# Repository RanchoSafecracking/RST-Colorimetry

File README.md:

# RST-Colorimetry
Hardware and firmware for 2015 cheapo colorimeter.

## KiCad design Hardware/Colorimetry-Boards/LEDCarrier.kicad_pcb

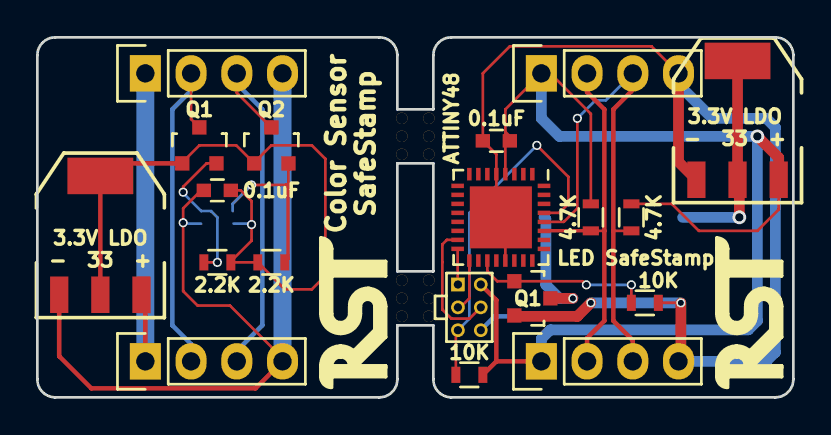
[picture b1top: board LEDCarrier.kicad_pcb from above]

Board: 2 copper layers, 42.0 x 20.0 mm, 21 parts (1 on the bottom side), 18 nets.

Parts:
C1, C2: 0.1uF; C_0603
D1: XREWHT-L1-0000-006E5; XR-E-2-SMD
IC1: ATTINY48-M; QFN-32-1EP_5x5mm_Pitch0.5mm
P1, P2, P4, P5: CONN_01X04; Pin_Header_Straight_1x04
P6: CONN_02X03; PIN-2x3-50MIL
Q1, Q2: 2N7002P; SOT-23
Q3: NTR4003N; SOT-23
R1, R2: 4700; R_0603
R3, R4: 2.2K; R_0603
R5, R6: 10K; R_0603
U1, U3: AP2114H-3.3TRG1; SOT223
U2: VEML6040; 4-TFLGA

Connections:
/+3.3V2: C2.1, Q1.1, Q2.1, R3.1, R4.1, U1.2, U2.4
/+5V2: P4.1, P5.1, U1.3
/GND2: C2.2, P4.4, P5.4, U1.1, U2.1
/SCL2: P4.3, P5.3, Q2.3
/SDA2: P4.2, P5.2, Q1.3
GND: C1.2, IC1.5, IC1.21, IC1.33, P1.4, P2.4, P6.6, Q3.2, R6.2, U3.1
LEDC: IC1.19, Q3.1, R6.1
MISO: IC1.16, P6.1
MOSI: IC1.15, P6.4
unnamed: D1.A, U3.2
unnamed: D1.C, Q3.3
unnamed: Q1.2, R3.2, U2.2
unnamed: Q2.2, R4.2, U2.3
RST: IC1.29, P6.5, R5.2
SCK: IC1.17, P6.3
SCL: IC1.28, P1.3, P2.3, R1.2
SDA: IC1.27, P1.2, P2.2, R2.2
VCC: C1.1, IC1.4, P1.1, P2.1, P6.2, R1.1, R2.1, R5.1, U3.3

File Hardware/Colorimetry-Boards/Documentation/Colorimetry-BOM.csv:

Designator,Digi-Key Part Number,Manufacturer,Manufacturer Part Number,Quantity 1,Mfg Std Lead Time,Description
"U1,U3",AP2114H-3.3TRG1DICT-ND,DIODES INCORPORATED (VA),AP2114H-3.3TRG1,2,5 Weeks,IC REG LDO 3.3V 1A SOT223
U2,VEML6040A3OGCT-ND,VISHAY SEMICONDUCTOR OPTO DIVISION (VA),VEML6040A3OG,1,6 Weeks,RGBW COLOR SENSOR I2C INTERFACE
"Q1,Q2",568-5818-1-ND,NXP SEMICONDUCTORS (VA),"2N7002P,215",2,6 Weeks,MOSFET N-CH 60V 0.36A SOT-23
"C1,C2",311-1335-1-ND,YAGEO (VA),CC0603KPX7R7BB104,2,25 Weeks,CAP CER 0.1UF 16V X7R 0603
IC1,ATTINY48-MU-ND,ATMEL,ATTINY48-MU,1,6 Weeks,IC MCU 8BIT 4KB FLASH 32QFN
D1,XREWHT-L1-0000-006E5CT-ND,CREE INC (VA),XREWHT-L1-0000-006E5,1,6 Weeks,LED XLAMP NEUTRAL WHT 4000K 2SMD
Q3,NTR4003NT1GOSCT-ND,ON SEMICONDUCTOR (VA),NTR4003NT1G,1,10 Weeks,MOSFET N-CH 30V 500MA SOT-23
"R3,R4",311-2.2KGRCT-ND,YAGEO (VA),RC0603JR-072K2L,2,22 Weeks,RES SMD 2.2K OHM 5% 1/10W 0603
"R1,R2",311-4.7KGRCT-ND,YAGEO (VA),RC0603JR-074K7L,2,22 Weeks,RES SMD 4.7K OHM 5% 1/10W 0603
"R5,R6",311-10KGRCT-ND,YAGEO (VA),RC0603JR-0710KL,2,22 Weeks,RES SMD 10K OHM 5% 1/10W 0603
"P1,P2,P3,P4",A1927-ND,TE CONNECTIVITY AMP,640457-4,4,10 Weeks,CONN HEADER RTANG 4POS .100 TIN
P6,S9015E-03-ND,SULLINS CONNECTOR SOLUTIONS,GRPB032VWVN-RC,1,4 Weeks,"CONN HEADER .050"" 6POS DL PCB AU"

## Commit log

2015-11-06 Punctuated
    Teaching about github
2015-11-06 Started LED Carrier Board
2015-11-10 Finished Schematic, Started Layout
    Finished schematic and layout of color sensor as well
2015-11-10 Renaming and finished boards
    Also reworked color sensor board
2015-11-12 Finished Hardware
    Now we wait for it all to arrive
2015-11-12 Added Unit Cost
2015-11-13 Spent more money
    Added obscure 50mil 6pos IDC connector for ISP programming the attiny
